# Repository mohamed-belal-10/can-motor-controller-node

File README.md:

# CAN-Connected Closed-Loop DC Motor Controller Node

A single PCB "smart joint" for robot arms, rovers, or any multi-actuator robotic
system: it bolts onto a DC gearmotor, closes a cascaded current → speed →
position control loop locally on an STM32, and takes setpoints over a shared
CAN bus instead of running dedicated wires back to a central controller.
Multiple nodes share one twisted-pair CAN bus, each addressed independently.

A portfolio project by **Mohamed Belal ("Belo")** — Mechatronics Engineering,
GUC.

---

## Why this project

- **First board with a real power stage.** Current in the amps range, not the
  milliamps of a typical digital-signal board — Kelvin sensing considerations,
  thermal copper, and return-path separation under switching noise.
- **Introduces CAN bus** as a communication protocol, end to end: transceiver
  hardware, bxCAN peripheral configuration, bit-timing, and a companion
  USB-CAN adapter to test it from a laptop.
- **Introduces cascaded multi-loop control** (current → speed → position),
  the conceptual step up from a single-loop PID.
- Built from and cross-checked against two open reference designs: CVRA's
  `motor-control-board` (KiCad, CC-BY) and Cormack's STM32L433 motor driver.

---

## System overview

```
                    ┌──────────────┐      ┌──────────────┐
   12V IN  ────────▶│ LM2596S-5V   │─5V──▶│ AMS1117-3.3  │────▶ 3.3V rail
   (motor            │ buck (switch)│      │ LDO (linear) │      │
    supply)          └──────────────┘      └──────────────┘      │
        │                                                          │
        │ (direct, unregulated)                                    │
        ▼                                                          ▼
   ┌──────────┐    PWM x2      ┌──────────┐   IPROPI    ┌─────────────┐
   │ DRV8874  │◀───────────────│ STM32F103│◀────────────│ (internal to │
   │ H-bridge │                │  C8T6    │             │  DRV8874)    │
   └────┬─────┘                └────┬─────┘             └─────────────┘
        │ motor terminals            │  I²C
        ▼                            ▼
   ┌──────────┐                ┌──────────┐        ┌──────────────┐
   │ DC MOTOR │────coupled────▶│  AS5600  │        │ SN65HVD230   │◀──▶ CAN H/L
   │          │  (shaft end)   │ (angle)  │        │ (transceiver)│    to bus
   └──────────┘                └──────────┘        └──────────────┘
```

Two boards are designed here:

| Board | Role | Location |
|---|---|---|
| **`motor_controller`** | Main node — MCU, power stage, H-bridge, CAN interface | [`hardware/motor_controller/`](hardware/motor_controller/) |
| **`AS5600_Encoder_Node`** | Small sub-PCB carrying the bare AS5600 angle sensor, linked to the main board over a 4-pin JST-SH cable | [`hardware/AS5600_Encoder_Node/`](hardware/AS5600_Encoder_Node/) |

The AS5600 lives on its own tiny PCB — not a generic breakout module —
specifically so the main board's own calculated I²C pull-up resistors are
the *only* pull-ups on the bus (most off-the-shelf breakout modules bundle
their own, which would silently change the bus's effective pull-up value).

---

## Gallery

### Main board — `motor_controller`

<table>
<tr>
<td width="50%">

**PCB layout** (KiCad, top copper + silkscreen)

</td>
<td width="50%">

**3D render**

</td>
</tr>
</table>

### Sub-board — `AS5600_Encoder_Node`

<table>
<tr>
<td width="50%">

**PCB layout**

</td>
<td width="50%">

**3D render**

</td>
</tr>
</table>

---

## Repository structure

```
.
├── README.md
├── LICENSE
├── docs/                                       Design documentation
│   ├── CAN_Motor_Controller_Node_Spec.md           Full BOM, design decisions, CAN protocol, pin map
│   └── CAN_Motor_Controller_Node_PCB_Layout_Guidelines.md   Placement, routing, plane strategy, DRC targets
└── hardware/
    ├── motor_controller/                       Main CAN motor controller node
    │   ├── motor_controller.kicad_pro/.kicad_sch/.kicad_pcb/.kicad_prl
    │   ├── PCB_design.png                          PCB layout screenshot
    │   ├── hardware_design.png                     3D render
    │   └── manufacturing/
    │       ├── gerbers/                            Gerber + drill files
    │       └── motor_controller-gerbers.zip         Fab-ready zip (JLCPCB format)
    └── AS5600_Encoder_Node/                    AS5600 magnetic encoder sub-PCB
        ├── AS5600_Encoder_Node.kicad_pro/.kicad_sch/.kicad_pcb/.kicad_prl
        ├── PCB_design.png                          PCB layout screenshot
        ├── hardware_design.png                     3D render
        └── manufacturing/
            ├── gerbers/
            └── AS5600_Encoder_Node-gerbers.zip
```

All KiCad projects are **KiCad 8+** format.

---

## Main board — `motor_controller`

### Core components

| Subsystem | Part | Notes |
|---|---|---|
| MCU | STM32F103C8T6 (LQFP-48) | 72 MHz, bxCAN, runs all 3 PID loops + CAN stack |
| Clock | 8 MHz HSE crystal, C_L = 20 pF | Required for reliable 500 kbps CAN bit timing (HSI is too loose) |
| Motor driver | DRV8874 (HTSSOP-16, PowerPAD) | Integrated current sense (IPROPI) and cycle-by-cycle current chopping — no external shunt/amplifier needed |
| Power stage | LM2596S-5V (buck) → AMS1117-3.3 (LDO) | Two-stage: switching for efficiency, then linear to give the current-sense ADC a clean reference |
| CAN transceiver | SN65HVD230 (SOIC-8) | 3.3V-only, high-speed mode, `NUP2105L` TVS array for bus ESD protection |
| Encoder | AS5600 (on its own sub-PCB) | 12-bit absolute angle over I²C — see below |
| Actuator | JGA25-370, 12V, 133 RPM, 20 kg·cm | Brushed DC gearmotor, 1:78 gearbox |

### Electrical specs

- **Motor supply:** 12 V nominal (6–18 V DRV8874 range)
- **Current limit:** 2.0 A hardware trip (`I_TRIP`, VREF divider-set), cycle-by-cycle chopping
- **PWM switching frequency:** 20 kHz (H-bridge), 150 kHz (buck)
- **Stackup:** 4-layer — L1 signal, L2 solid GND, L3 split power (VM/3.3V), L4 signal
- **CAN bus:** 500 kbps, standard 11-bit IDs, JST-XH 3-pos daisy-chain connectors (IN/OUT), jumper-selectable 120 Ω termination

### CAN protocol

| Frame | Direction | ID | Payload |
|---|---|---|---|
| Command | host → node | `0x100 + node_id` | `float32` setpoint, `uint8` mode (0=position, 1=speed, 2=current) |
| Telemetry | node → host | `0x200 + node_id` | `float32` position, `uint16` current (mA), `uint8` fault flags |

`node_id` is assigned in firmware at flash time — no address jumpers on the
board.

### Design status

- ✅ All five schematic sheets complete (Power Stage, MCU Core, Motor Drive,
  CAN Bus, Sensing), ERC clean.
- ✅ Every component value and part number closed, across four audit passes
  (full history in [`docs/CAN_Motor_Controller_Node_Spec.md`](docs/CAN_Motor_Controller_Node_Spec.md)).
- ✅ Layout complete; gerbers generated (see `manufacturing/`).
- ⚠️ **Flagged, unresolved:** DRV8874 power-up sequencing (VCC vs. VM order)
  not verified against the datasheet.
- ⚠️ **Open before re-ordering:** cross-check the main board's AS5600 link
  connector pin order against the sub-PCB's `J1`/`J7` connector — both
  footprints were placed independently.
- 🚚 **Externally sourced, not yet in hand:** DRV8874 (not stocked locally —
  ordered internationally), diametrically-magnetized magnet (must confirm
  magnetization type with seller before buying).

---

## Sub-board — `AS5600_Encoder_Node`

A minimal breakout for the bare AS5600 magnetic rotary position sensor
(SOP-8), designed specifically to avoid the double-pull-up problem that
off-the-shelf AS5600 modules introduce.

| Item | Detail |
|---|---|
| Sensor | AS5600 (SOP-8), 12-bit absolute angle over I²C |
| Power wiring | `VDD5V` and `VDD3V3` tied together, fed from the main board's 3.3V rail (required for correct 3.3V single-supply operation per datasheet) |
| Decoupling | 100 nF + 10 µF in parallel across the tied VDD node → GND (matches datasheet Fig. 13, 3.3V-mode) |
| Direction select | 3-pad solder jumper (`DIR`: GND = CW-increasing, VDD = CCW-increasing) — bridged at assembly time once motor orientation is known |
| Link to main board | JST-SH, 1.0 mm pitch, 4-position — carries `+3V3`, `SCL`, `SDA`, `GND` |
| Mounting | Glued flat to the motor's rear shaft-stub end face, read through a 1.0–1.5 mm air gap by a 6 mm diametric NdFeB magnet |
| Encoder resolution | 4096 counts/rev at the motor shaft → 319,488 counts/rev at the JGA25-370's output shaft (through its 1:78 gearbox) |

The AS5600 mounting bracket (clamp-style, sized to the motor's 25 mm body OD)
is specified mechanically in [`docs/CAN_Motor_Controller_Node_Spec.md`](docs/CAN_Motor_Controller_Node_Spec.md#9-as5600-mounting-bracket-mechanical-spec--solidworks-task)
but deliberately not finalized until the physical sub-PCB and motor are in
hand to confirm dimensions.

---

## Documentation

| Document | Covers |
|---|---|
| [`docs/CAN_Motor_Controller_Node_Spec.md`](docs/CAN_Motor_Controller_Node_Spec.md) | Full BOM with sourcing/pricing notes, design-decision rationale, CAN protocol definition, STM32 pin assignment tracker, CAN-adapter companion tool, AS5600 mounting bracket spec |
| [`docs/CAN_Motor_Controller_Node_PCB_Layout_Guidelines.md`](docs/CAN_Motor_Controller_Node_PCB_Layout_Guidelines.md) | Trace sizing, via strategy, floorplan, placement rules, ground/power plane strategy, CAN routing, thermal, DRC targets, pre-routing checklist |

---

## Build sequence

1. Schematic capture (CAN node + power stage + DRV8874 + AS5600) — **done**
2. ERC clean — **done**
3. Layout — **done**
4. DRC clean, JLCPCB stackup check, order
5. Bring-up: power rails → CAN enumeration → AS5600 sanity read → close current loop → speed loop → position loop
6. Bring up the companion CAN-USB adapter and drive the node from a laptop with real command/telemetry frames

Full detail on each step, including the CAN-USB adapter's own BOM, wiring,
and firmware plan, is in [`docs/CAN_Motor_Controller_Node_Spec.md`](docs/CAN_Motor_Controller_Node_Spec.md#7-build-sequence).

---

## Fabrication

Both boards are designed for JLCPCB (4-layer main board, 2-layer sub-PCB).
Ready-to-upload gerber/drill packages are checked in under each board's
`manufacturing/` folder. Re-export from KiCad's Plot dialog after any layout
change rather than editing the checked-in gerbers by hand.

## Reference designs

- [CVRA `motor-control-board`](https://github.com/cvra) — KiCad, CC-BY, near-identical spec; source for the CAN daisy-chain connector and termination-jumper approach.
- Cormack's STM32L433 motor driver — single-board layout reasoning, undervoltage-lockout-as-safety-feature technique.

## License

MIT — see [`LICENSE`](LICENSE).

This repository contains PCB hardware design files (KiCad schematics,
layouts, and manufacturing outputs) alongside documentation. The MIT License
is applied for simplicity and consistency with the author's other portfolio
repositories; no warranty is made or implied about the fitness of any
hardware design herein for use with live mains, high-current, or
safety-critical applications. Build and operate at your own risk.

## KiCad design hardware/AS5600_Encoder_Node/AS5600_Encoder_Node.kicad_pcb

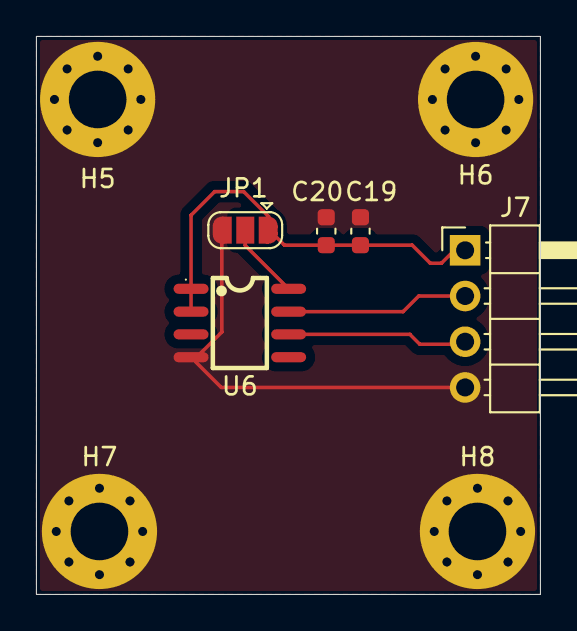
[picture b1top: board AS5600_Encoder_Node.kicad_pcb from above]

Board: 2 copper layers, 28.0 x 31.0 mm, 9 parts (0 on the bottom side), 5 nets.

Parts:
C19: 100nF; C_0603_1608Metric
C20: 10uF; C_0603_1608Metric
H5, H6, H7, H8: MountingHole_Pad; MountingHole_3.2mm_M3_Pad_Via
J7: Conn_01x04; PinHeader_1x04_P2.54mm_Horizontal
JP1: SolderJumper_3_Open; SolderJumper-3_P1.3mm_Open_RoundedPad1.0x1.5mm
U6: AS5600-ASOT; SOIC-8_L5.0-W4.0-P1.27-LS6.0-BL

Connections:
+3V3: C19.1, C20.1, J7.1, JP1.1 (A), U6.1 (VDD5V), U6.2 (VDD3V3)
/AS5600_Encoder/DIR: JP1.2 (C), U6.8 (DIR)
/SCL: J7.2, U6.7 (SCL)
/SDA: J7.3, U6.6 (SDA)
GND: C19.2, C20.2, H5.1, H6.1, H7.1, H8.1, J7.4, JP1.3 (B), U6.4 (GND)

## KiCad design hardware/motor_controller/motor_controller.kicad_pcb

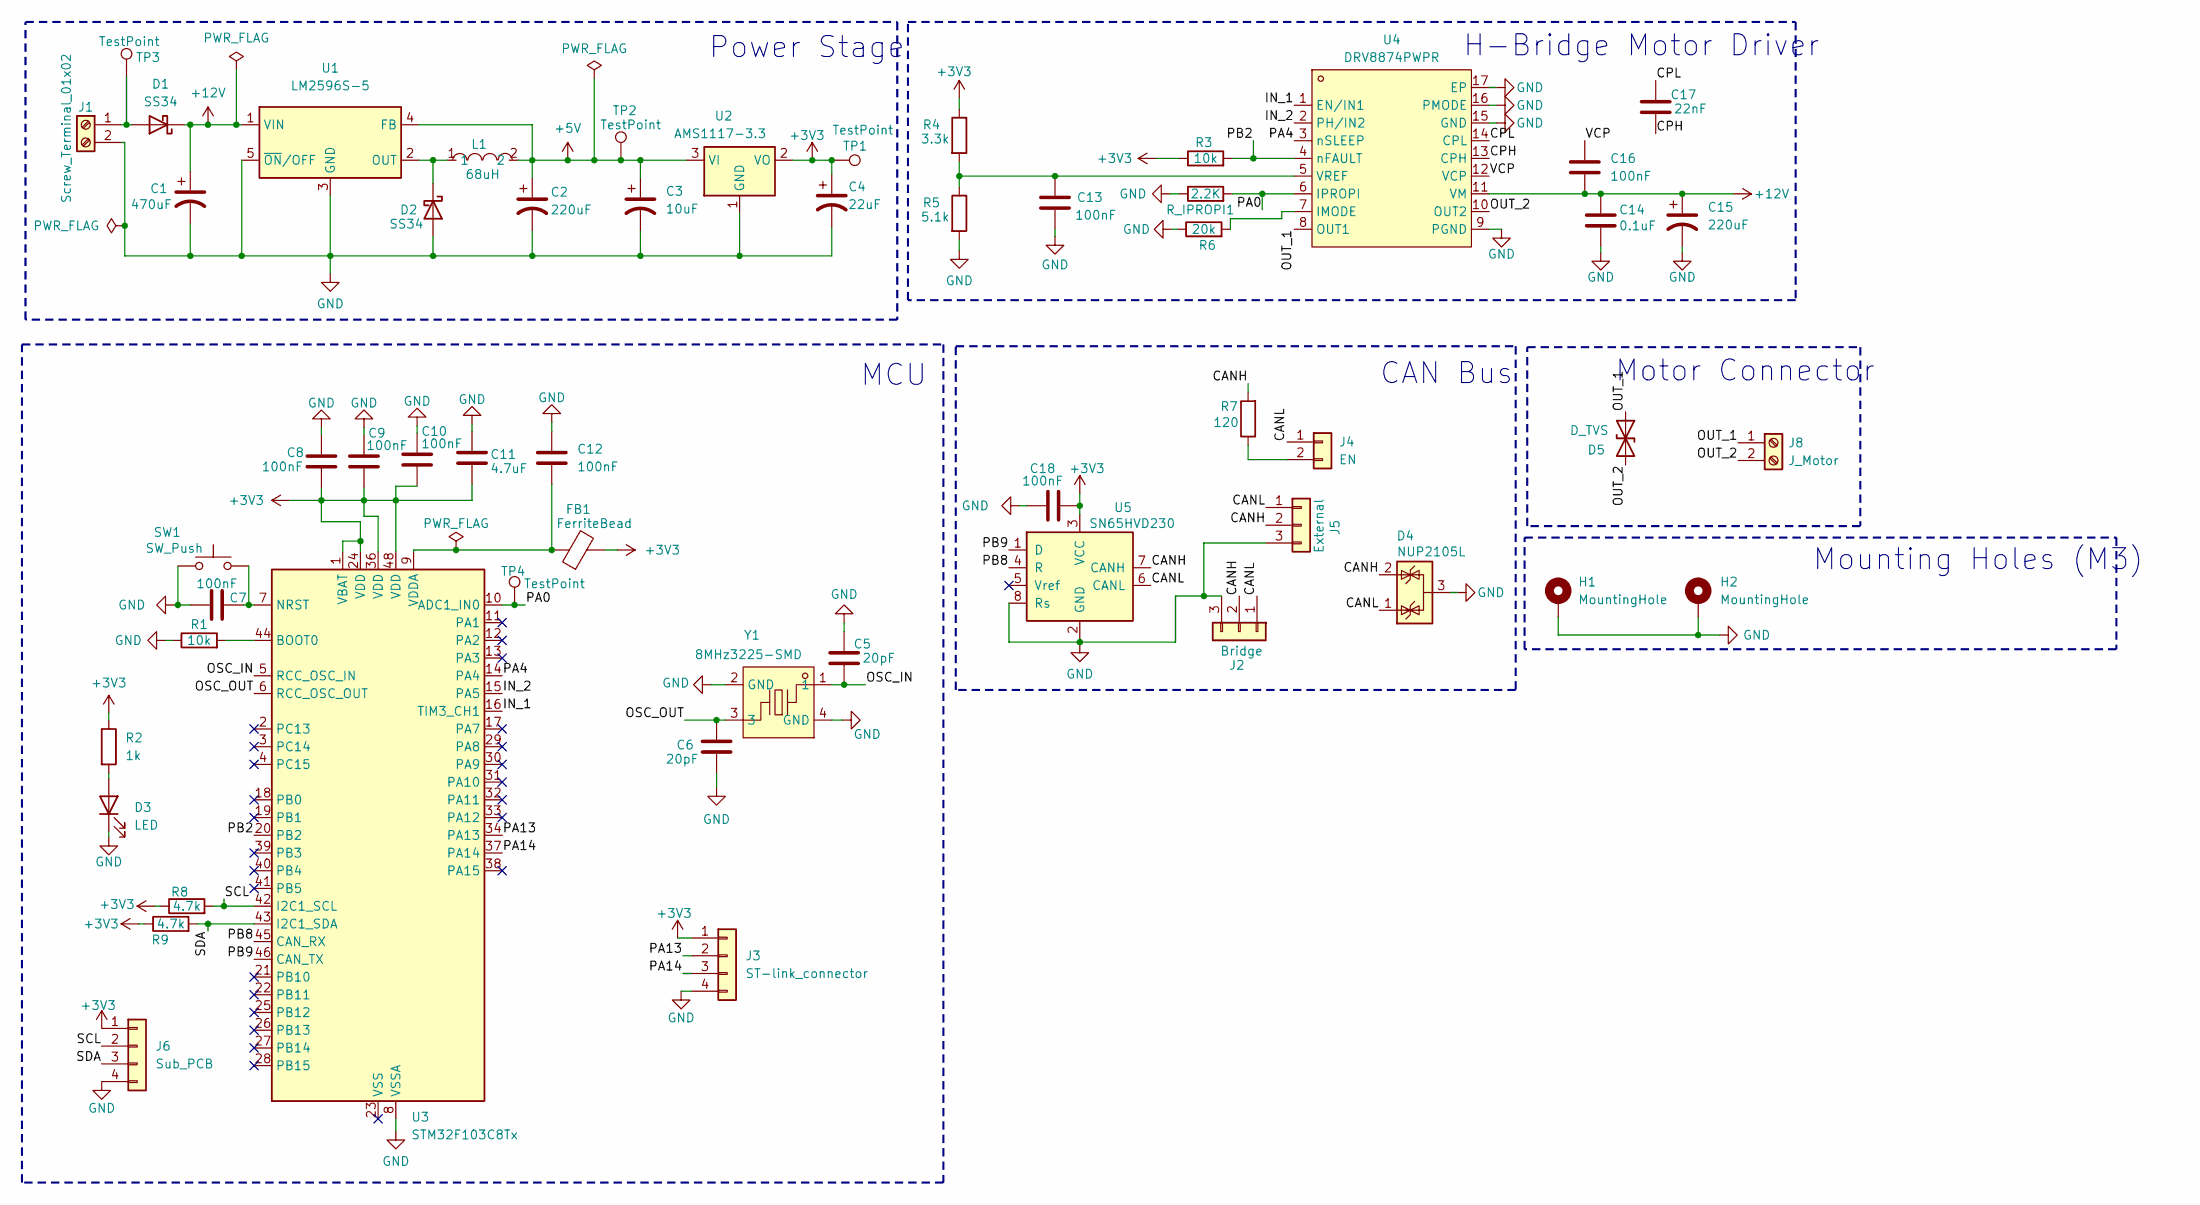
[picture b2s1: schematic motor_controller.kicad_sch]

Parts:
C1: 470uF; CP_Radial_D8.0mm_P3.50mm
C2, C15: 220uF; CP_Radial_D8.0mm_P3.50mm
C3: 10uF; CP_Radial_D8.0mm_P3.50mm
C4: 22uF; CP_Radial_D8.0mm_P3.50mm
C5, C6: 20pF; C_0603_1608Metric
C7, C8, C9, C10, C12, C13, C16, C18: 100nF; C_0603_1608Metric
C11: 4.7uF; C_0603_1608Metric
C14: 0.1uF; C_0603_1608Metric
C17: 22nF; C_0603_1608Metric
D1, D2: SS34; D_SMA
D3: LED; LED_0805_2012Metric
D4: NUP2105L; SOT-23
D5: D_TVS; D_SMA
FB1: FerriteBead; L_0805_2012Metric
H1, H2: MountingHole; MountingHole_3.2mm_M3_Pad_Via
J1: Screw_Terminal_01x02; TerminalBlock_Phoenix_MKDS-1,5-2-5.08_1x02_P5.08mm_Horizont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
J2: Bridge; JST_XH_S3B-XH-A_1x03_P2.50mm_Horizontal
J3: ST-link_connector; PinHeader_1x04_P2.54mm_Horizontal
J4: EN; PinHeader_1x02_P2.54mm_Vertical
J5: External; JST_XH_S3B-XH-A_1x03_P2.50mm_Horizontal
J6: Sub_PCB; PinHeader_1x04_P2.54mm_Horizontal
J8: J_Motor; TerminalBlock_Phoenix_MKDS-1,5-2-5.08_1x02_P5.08mm_Horizont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
L1: 68uH; IND-SMD_L12.3-W12.3_SMDRI127; MPN SMDRI127-680MT; LCSC Part C9907
R1, R3: 10k; R_0603_1608Metric
R2: 1k; R_0603_1608Metric
R4: 3.3k; R_0603_1608Metric
R5: 5.1k; R_0603_1608Metric
R6: 20k; R_0603_1608Metric
R7: 120; R_0603_1608Metric
R8, R9: 4.7k; R_0603_1608Metric
R_IPROPI1: 2.2K; R_0603_1608Metric
SW1: SW_Push; SW_SPST_PTS645Sx43SMTR92
TP1, TP2, TP3, TP4: TestPoint; TestPoint_Pad_D1.5mm
U1: LM2596S-5; TO-263-5_TabPin3
U2: AMS1117-3.3; SOT-223-3_TabPin2
U3: STM32F103C8Tx; LQFP-48_7x7mm_P0.5mm
U4: DRV8874PWPR; HTSSOP-16_L5.0-W4.4-P0.65-LS6.4-BL-EP; MPN DRV8874PWPR; LCSC Part C1855818
U5: SN65HVD230; SOIC-8_3.9x4.9mm_P1.27mm
Y1: 8MHz3225-SMD; CRYSTAL-SMD_4P-L3.2-W2.5-BL; MPN TAXM8M4RLBDDT2T; LCSC Part C720915

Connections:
+3V3: C4.1, C8.2, C9.2, C10.2, C11.2, C18.2, FB1.2, J3.1 (3V3), J6.1, R2.1, R3.1, R4.1, R8.1, R9.1, TP1.1, U2.2 (VO), U3.1 (VBAT), U3.24 (VDD), U3.36 (VDD), U3.48 (VDD), U5.3 (VCC)
+5V: C2.1, C3.1, L1.2, TP2.1, U1.4 (FB), U2.3 (VI)
+12V: C1.1, C14.1, C15.1, C16.1, D1.1 (K), U1.1 (VIN), U4.11 (VM)
/CANH: D4.2 (K), J2.2, J5.2, R7.2, U5.7 (CANH)
/CANL: D4.1 (K), J2.1, J4.1, J5.1, U5.6 (CANL)
/CPH: C17.2, U4.13 (CPH)
/CPL: C17.1, U4.14 (CPL)
/IN_1: U3.16 (TIM3_CH1), U4.1 (EN/IN1)
/IN_2: U3.15 (PA5), U4.2 (PH/IN2)
/OSC_IN: C5.2, U3.5 (RCC_OSC_IN), Y1.1
/OSC_OUT: C6.1, U3.6 (RCC_OSC_OUT), Y1.3
/OUT_1: D5.1 (A1), J8.1, U4.8 (OUT1)
/OUT_2: D5.2 (A2), J8.2, U4.10 (OUT2)
/PA0: R_IPROPI1.2, TP4.1, U3.10 (ADC1_IN0), U4.6 (IPROPI)
/PA4: U3.14 (PA4), U4.3 (nSLEEP)
/PA13: J3.2 (SWDIO), U3.34 (PA13)
/PA14: J3.3 (SWCLK), U3.37 (PA14)
/PB2: R3.2, U3.20 (PB2), U4.4 (nFAULT)
/PB8: U3.45 (CAN_RX), U5.4 (R)
/PB9: U3.46 (CAN_TX), U5.1 (D)
/SCL: J6.2, R8.2, U3.42 (I2C1_SCL)
/SDA: J6.3, R9.2, U3.43 (I2C1_SDA)
/VCP: C16.2, U4.12 (VCP)
GND: C1.2, C2.2, C3.2, C4.2, C5.1, C6.2, C7.1, C8.1, C9.1, C10.1, C11.1, C12.1, C13.2, C14.2, C15.2, C18.1, D2.2 (A), D3.1 (K), D4.3 (A), H1.1, H2.1, J1.2, J2.3, J3.4 (GND), J5.3, J6.4, R1.1, R5.2, R6.1, R_IPROPI1.1, SW1.1, U1.3 (GND), U1.5 (~ON/OFF), U2.1 (GND), U3.8 (VSSA), U4.9 (PGND), U4.15 (GND), U4.16 (PMODE), U4.17 (EP), U5.2 (GND), U5.8 (Rs), Y1.2 (GND), Y1.4 (GND)
unnamed: D1.2 (A), J1.1, TP3.1
unnamed: D2.1 (K), L1.1, U1.2 (OUT)
unnamed: D3.2 (A), R2.2
unnamed: J4.2, R7.1
unnamed: R1.2, U3.44 (BOOT0)
unnamed: C7.2, SW1.2, U3.7 (NRST)
unnamed: C12.2, FB1.1, U3.9 (VDDA)
unnamed: R6.2, U4.7 (IMODE)
unnamed: C13.1, R4.2, R5.1, U4.5 (VREF)

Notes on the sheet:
CAN Bus
Motor Connector
Power Stage
H-Bridge Motor Driver
MCU
Mounting Holes (M3)

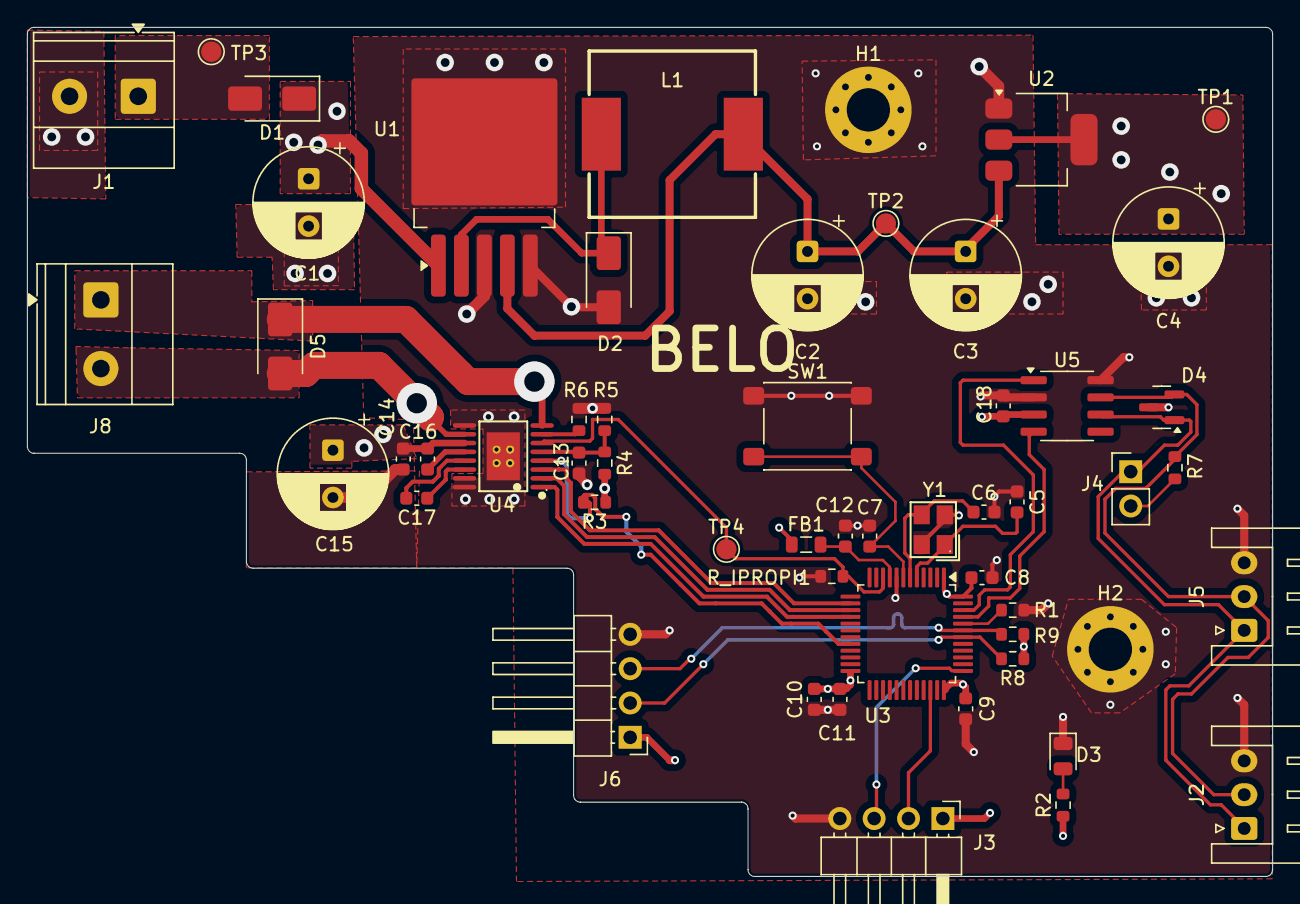
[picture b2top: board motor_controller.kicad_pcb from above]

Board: 4 copper layers, 92.1 x 62.8 mm, 55 parts (0 on the bottom side), 33 nets.
